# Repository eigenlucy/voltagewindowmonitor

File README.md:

# Voltage Window Monitor

This package defines an atopile component for a voltage window monitor based on the ATL431LI shunt regulator.

See the [ATL431 Datasheet System Examples (Figure 37)](https://www.ti.com/lit/ds/symlink/atl431li.pdf?ts=1744777182166) for more details

```mermaid
graph TD
    subgraph "Voltage Window Monitor Concept (from README)"
        A[Input Voltage Vin] --> B{High Threshold Check}
        A --> C{Low Threshold Check}

        subgraph "High Threshold Path"
            direction LR
            B --> D[Voltage Divider R1A, R2A]
            D --> E[Reg1]
            E -- Compare with Vref --> F{Vin > V_high?}
        end

        subgraph "Low Threshold Path"
            direction LR
            C --> G[Voltage Divider R1B, R2B]
            G --> H[Reg2]
            H -- Compare with Vref --> I{Vin < V_low?}
        end

        F --> J{Output Logic}
        I --> J
        J --> K[Final Output (High if Vin is within window, Low otherwise)]
    end
```

## Threshold Equations

The high and low voltage thresholds are set using external resistor dividers connected to the REF pin of two separate ATL431LI devices (or similar comparators with an internal reference). The threshold is triggered when the voltage at the REF pin equals the internal reference voltage (`Vref`, typically 2.5V).

- **High Threshold (V_high):**

  ```
  V_high = Vref * (1 + R1A / R2A)
  ```

  Where R1A and R2A form the voltage divider for the high threshold comparator.

- **Low Threshold (V_low):**

  ```
  V_low = Vref * (1 + R1B / R2B)
  ```

  Where R1B and R2B form the voltage divider for the low threshold comparator.

## Todo

- Automatically solve resistor values with assertions given Vin, Ika_min, Iref_min, etc

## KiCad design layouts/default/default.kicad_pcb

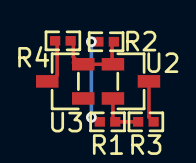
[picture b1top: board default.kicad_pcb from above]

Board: 2 copper layers, 6 parts (0 on the bottom side), 5 nets.

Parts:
R1, R2, R3, R4: 10kΩ ±1% 62.5mW; R0402-56259e
U2, U3: SOT-23-3_L2.9-W1.3-P1.90-LS2.4-BR-688f29

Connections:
A: R3.2, U2.3
REF: R1.2, R3.1, U2.2
REF-1: R2.2, R4.1, U2.1, U3.2
gnd: R4.2, U3.3
hv: R1.1, R2.1

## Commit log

2025-04-16 intial build
2025-04-16 testing package workflow
2025-04-16 fixed ci.yml version set
2025-04-16 fixed PCB layout + ci.yml
2025-04-16 added checklist + semver version :woozy:
2025-04-16 added ato-version
2025-04-16 removed to version
2025-04-16 fixed
2025-04-17 new readme
2025-04-17 better docs, removed LED
2025-04-17 smoother readme
2025-04-18 added mermaid diagram
